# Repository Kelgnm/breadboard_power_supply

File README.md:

# Breadboard 5V Power Supply (LM7805)

- Converts an input DC voltage (recommended 7–12V) into a stable 5V output using an LM7805 voltage regulator. This can be used to power 5V devices such as sensors and small embedded circuits.
- Connections: Connect a DC power adapter to the barrel jack input, and obtain regulated 5V and GND from the output pin headers.
- This project was created to learn KiCad and basic power supply design. It represents my early steps into hardware development and PCB layout. (inspiration from Ikarthikmb)

---

| 3D View |
|---------|
|  |

| Schematic Diagram |
|---------|
|  |

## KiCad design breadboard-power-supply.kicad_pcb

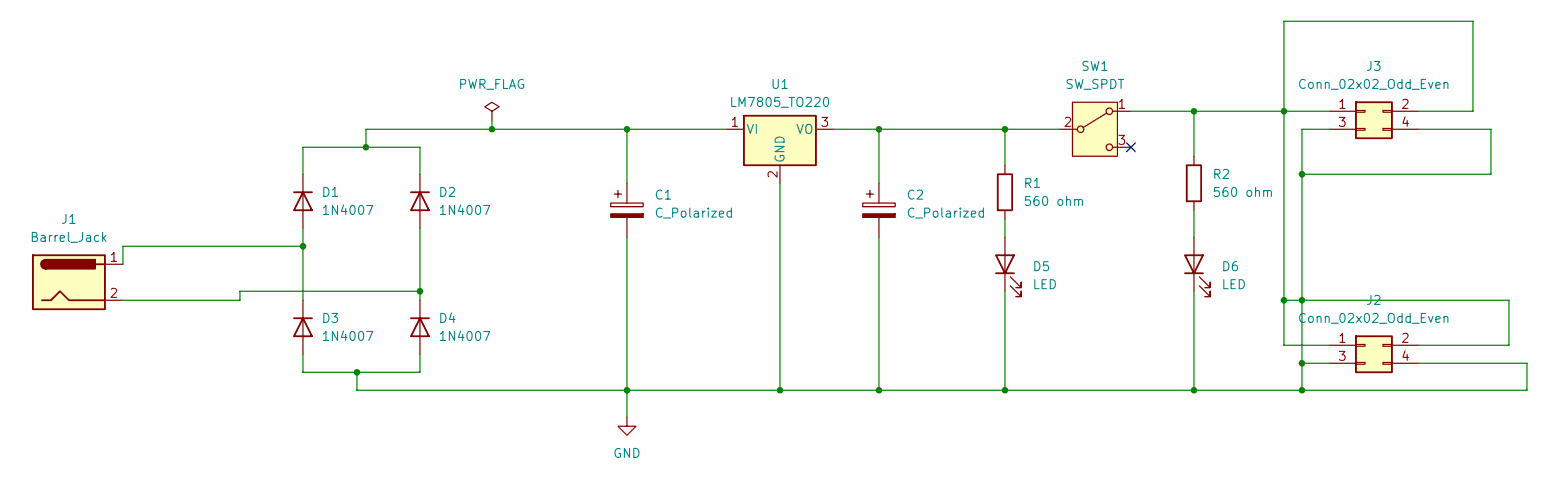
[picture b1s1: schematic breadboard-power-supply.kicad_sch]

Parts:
C1, C2: C_Polarized; CP_Radial_D10.0mm_P5.00mm
D1, D2, D3, D4: 1N4007; D_DO-41_SOD81_P10.16mm_Horizontal
D5, D6: LED; LED_D5.0mm
J1: Barrel_Jack; BarrelJack_Switchcraft_L721RAU
J2, J3: Conn_02x02_Odd_Even; PinHeader_2x02_P2.54mm_Vertical
R1, R2: 560 ohm; R_Axial_DIN0207_L6.3mm_D2.5mm_P2.54mm_Vertical
SW1: SW_SPDT; button_switch
U1: LM7805_TO220; TO-220-3_Vertical

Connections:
GND: C1.2, C2.2, D3.2 (A), D4.2 (A), D5.1 (K), D6.1 (K), J2.1, J2.2, J2.3, J2.4, J3.1, J3.2, J3.3, J3.4, R2.1, SW1.1 (A), U1.2 (GND)
unnamed: D1.2 (A), D3.1 (K), J1.1
unnamed: C1.1, D1.1 (K), D2.1 (K), U1.1 (VI)
unnamed: D2.2 (A), D4.1 (K), J1.2
unnamed: D5.2 (A), R1.2
unnamed: D6.2 (A), R2.2
unnamed: C2.1, R1.1, SW1.2 (B), U1.3 (VO)

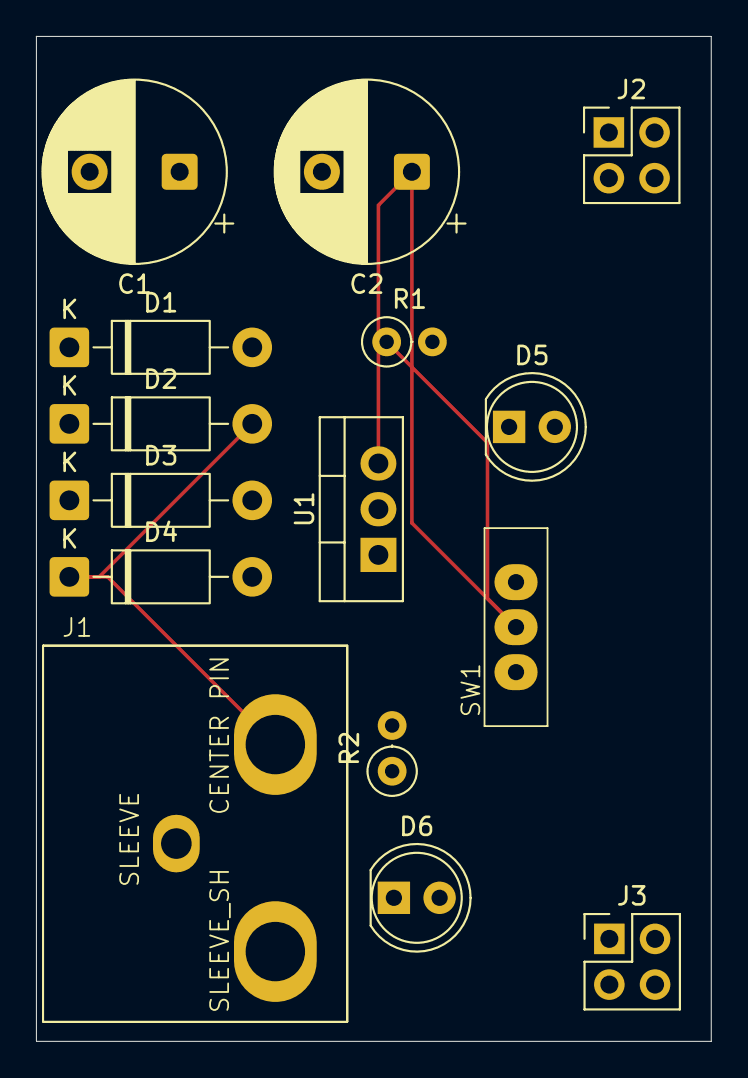
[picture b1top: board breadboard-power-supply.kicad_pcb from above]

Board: 2 copper layers, 37.5 x 55.8 mm, 15 parts (0 on the bottom side), 7 nets.

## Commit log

2026-02-21 Add README with project overview and images
2026-02-21 Replace images with table format in README
2026-02-21 Fix formatting in README.md for diagrams
2026-02-21 Clean up table formatting in README
    Removed unnecessary table headers from README.
2026-02-21 Revise README for clarity and formatting
    Updated project description and improved formatting.
